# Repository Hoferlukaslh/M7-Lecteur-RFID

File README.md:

# M7-Lecteur-RFID
Ce dépôt contient l'ensemble des éléments du projet « Prototype de lecteur RFID » développé dans le cadre du module M7.    
L'objectif principal est de concevoir un système embarqué compact et bon marché, destiné à être dupliqué au sein des cellules de production des locaux de la NewTec.    
   
Ce système agit comme une interface physique et logique entre des tags RFID et un automate (PLC).   

[- Lien vers le dépot --](https://github.com/Hoferlukaslh/M7-Lecteur-RFID)

## Détails du projet 

### Architecture Globale et Communication
Le lecteur utilise une architecture de communication hybride pour s'adapter aux différents besoins de la ligne de production :

- Communication Automate (PLC) : Le système est universel et s'intègre avec tout type de contrôleur (Wago, Beckhoff, Raspberry Pi, etc.). Cette communication, servant à transmettre les ordres et les données lues, peut être activée ou désactivée selon les besoins de la cellule.

- Communication API (Wi-Fi) : De manière indépendante, le système interagit avec un serveur Node-RED via des requêtes API HTTP pour mettre à jour l'emplacement des palettes en temps réel dans une base de données. 

```mermaid
flowchart TD
    %% Définition des nœuds
    NR[Node-RED]
    DB[(BDD)]
    M7[Projet M7]
    PLC[Automate]

    %% Définition des liens et des étiquettes
    NR --> DB
    NR <-.->|"Requête API HTTP<br>(WiFi)<br>MàJ emplacement <br>palettes"| M7
    PLC -->|"Communication<br>pour ordres<br>(désactivable)"| M7
```

### Spécifications Matérielles
Le dispositif est conçu pour fonctionner de manière autonome dans un environnement industriel.

- Microcontrôleur : Choix libre.
- Module RFID : SBC-RFID-RC522.
- Connectivité : Wi-Fi avec antenne (choix libre).
- Alimentation : 24V DC (standard industriel).
- Cibles RFID : Petits disques de 15 mm x 3 mm disposant d'une capacité de stockage maximale de 106 octets.
- Intégration mécanique : Boîtier de protection imprimé en 3D. Il assure la sécurité du PCB et de l'antenne, tout en proposant un design universel pour une fixation rapide sur n'importe quelle structure machine sans gêner le flux des palettes.

### Spécifications Logicielles
Le firmware embarqué gère à la fois l'antenne RFID et la communication avec l'automate.  

#### Librairie RFID
Une bibliothèque logicielle est intégrée pour gérer la mémoire restreinte des tags avec les fonctions suivantes :

| Fonction | Description | 
| --- | --- |
| READ | Lecture des données présentes. |
| WRITE | Écriture avec écrasement du contenu existant. |
| APPEND | Ajout de nouvelles données à la suite (via gestion de pointeurs/marqueurs). |
| DELETE ALL | Effacement complet ou formatage du tag. |

#### Logique de Contrôle

| Fonction | Description | 
| --- | --- |
| Démarrage/Arrêt | Piloté sur commande du PLC. |
| Badge lu avec succès | Retour du contenu formaté au PLC et envoi de la mise à jour de position au serveur Node-RED. |
| Badge illisible/Erreur | Retour d'un code d'erreur spécifique au PLC. |
| Badge défectueux | Retour d'un code d'erreur critique (HS) au PLC. |
| Aucun badge | État d'attente, aucune action. |

### Ressources utilisées
#### Logiciels
| Logo | Application | Version | Utilité | Licence |
| :---: | :--- | :--- | :--- | --- |
|  | [**OnlyOffice**](https://www.onlyoffice.com) | 9.3.1 | Suite bureautique utilisée pour la rédaction et l’édition des documents du projet (DOCX, XLSX). | AGPL-3.0 |
|  | [**Draw.io**](https://github.com/jgraph/drawio) | 29.3.6 | Outil de conception de diagrammes. Utilisé pour la conception UML. | Apache 2.0 |
|  | [**VSCodium**](https://vscodium.com/) | v1.116.02821 | Editeur de texte avec extension (IDE) | MIT |
|  | [**Arduino IDE**](https://www.arduino.cc/en/software/) | 2.3.8 | IDE pour framework arduino (C++) | AGPL-3.0 |

### Modèle de Données et Optimisation
La contrainte matérielle majeure est la limite de 106 octets par tag. Une optimisation des données est indispensable.

#### Données des Palettes
- Identifiant de la palette.  
- Contenu de la palette : Jusqu'à 6 articles stockés sous le format `TTT-XXXXXX-VV-R` (Type de l'article, Code unique, Version, Révision).

#### Données des Badges Client :
- Identifiant de la palette.  
- Pseudonyme du client (10 caractères).  
- Données de production pour 4 cellules : Date, heure, et identifiant de la cellule ayant effectué l'opération.

## Livrables Attendus
L'arborescence de ce projet est divisée selon les livrables suivants :  

| Livrables | Description | 
| --- | --- |
| [Hardware](./Hardware/) | Dossier électronique contenant les schémas de principe, le routage PCB (fichiers Gerber) et la nomenclature (BOM). |
| [Mechanical](./Firmware/) | Fichiers 3D (STL/STEP) pour l'impression du boîtier de protection. |
| [Firmware](./Firmware/) | Code source documenté du microcontrôleur, incluant la pile de communication et la librairie RFID. |
| [Documents](./Documents/) | CdC et Journal, Documentation technique du projet (Table de communication décrivant le protocole PLC, les endpoints de l'API HTTP, et la cartographie d'optimisation mémoire) |
| [Images](./Images/) | Dossier contenant des images utilisés dans le projet. |

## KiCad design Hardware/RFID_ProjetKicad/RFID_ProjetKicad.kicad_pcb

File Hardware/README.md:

Dossier électronique contenant les schémas de principe, le routage PCB (fichiers Gerber) et la nomenclature (BOM).

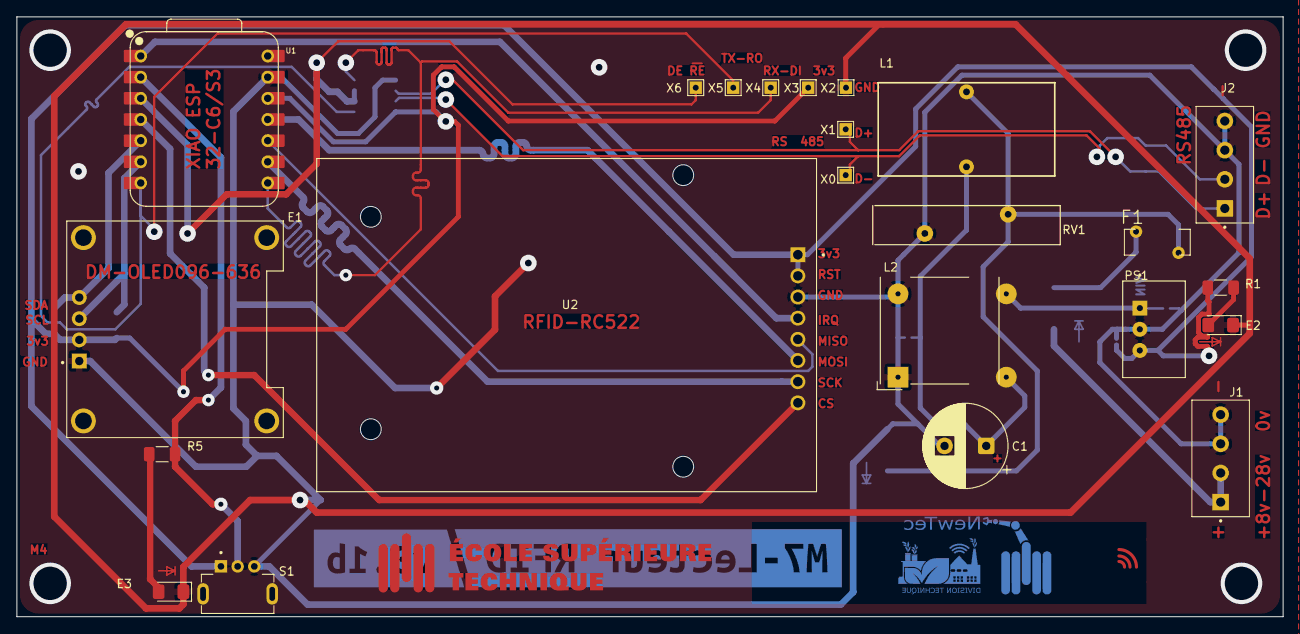
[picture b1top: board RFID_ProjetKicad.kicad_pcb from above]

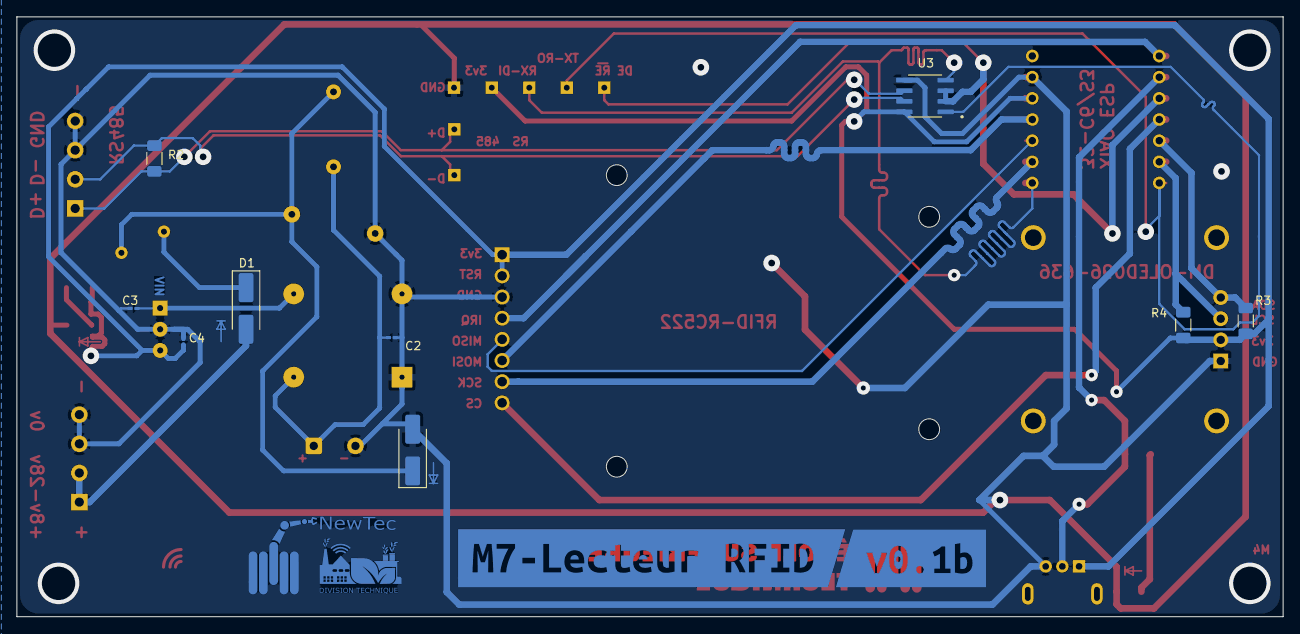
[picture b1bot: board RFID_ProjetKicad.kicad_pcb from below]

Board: 2 copper layers, 152.0 x 72.0 mm, 34 parts (11 on the bottom side), 22 nets.

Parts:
C1: 470µF; CP_Radial_D10.0mm_P5.00mm
C2: 4.7μF; C_0201_0603Metric_Pad0.64x0.40mm_HandSolder
C3: 10µF; C_0201_0603Metric_Pad0.64x0.40mm_HandSolder
C4: 22µF; C_0201_0603Metric_Pad0.64x0.40mm_HandSolder
D1: BX36_R1; D_SMA_Handsoldering
D2: SMAJ28A; D_SMA_Handsoldering
E1: DM-OLED096-636; MODULE_DM-OLED096-636
E2, E3: LED; LED_1206_3216Metric_Pad1.42x1.75mm_HandSolder
F1: PTC 1A; PTC
J1, J2: TB0011-350-04GR; SAMESKY_TB0011-350-04GR
L1: 300 µH; WE-FI_7447060
L2: 5 mH; SS11VL-11050
PS1: TSR_1-2433E; CONV_TSR_1-2433E
R1, R5: 68 R; R_1206_3216Metric_Pad1.30x1.75mm_HandSolder
R2: 120 R; R_1206_3216Metric_Pad1.30x1.75mm_HandSolder
R3, R4: 4k7; R_1206_3216Metric_Pad1.30x1.75mm_HandSolder
RV1: 20D470K; RV_Disc_D12mm_W4.7mm_P7.5mm
S1: SLW-874744; SW_SLW-874744-6A-RA-N-D
U1: XIAO-ESP32-C6-DIP
U2: RFID-RC522; MODULE_CEG006900
U3: MAX3485CSA_T; SOIC127P600X175-8N
X0, X1, X2, X3, X4, X5, X6: TestPoint_THTPad_1.5x1.5mm_Drill0.7mm
kibuzzard-6A1B3F22: G***; kibuzzard-6A1B3F22
kibuzzard-69FBB4E7: G***; kibuzzard-69FBB4E7

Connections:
+3V3: C4.1, E1.2 (VCC_IN), PS1.3 (+VOUT), R1.1, R3.1, R4.1, S1.1, U1.12 (3V3), U2.1 (VCC), U2.2 (RST), U3.8 (VCC), X3.1
+7V à 27.6V: D2.1 (A1), F1.2, L1.1, RV1.1
+8V à 28V: D1.2 (A), J1.1, J1.2
/D+: J2.1, R2.2, U3.6 (A), X1.1
/D-: J2.2, R2.1, U3.7 (B), X0.1
/SW_COM: R5.2, S1.2, U1.2 (GPIO1_A1_D1)
GND: C1.2, C2.2, C3.2, C4.2, D2.2 (A2), E1.1 (GND), E2.1 (K), E3.1 (K), J1.3, J1.4, J2.3, J2.4, L2.1, L2.4, PS1.2 (GND), RV1.2, S1.3, U1.13 (GND), U2.3 (GND), U3.5 (GND), X2.1
unnamed: C1.1, C2.1, L1.2, L2.2
unnamed: D1.1 (K), F1.1
unnamed: E1.3 (SCL), R4.2, U1.6 (GPIO23_D5_SCL)
unnamed: E1.4 (SDA), R3.2, U1.5 (GPIO22_D4_SDA)
unnamed: E2.2 (A), R1.2
unnamed: E3.2 (A), R5.1
unnamed: C3.1, L2.3, PS1.1 (+VIN)
unnamed: U1.1 (GPIO0_A0_D0), U2.4 (IRQ)
unnamed: U1.3 (GPIO2_A2_D2), U3.2 (~RE), U3.3 (DE), X6.1
unnamed: U1.7 (GPIO16_D6_TX), U3.1 (RO), X5.1
unnamed: U1.8 (GPIO17_D7_RX), U3.4 (DI), X4.1
unnamed: U1.11 (GPIO18_D10_MOSI), U2.6 (MOSI)
unnamed: U1.9 (GPIO19_D8_SCK), U2.7 (SCK)
unnamed: U1.10 (GPIO20_D9_MISO), U2.5 (MISO/SCL/TX)
unnamed: U1.4 (GPIO21_D3), U2.8 (SS/SDA/RX)

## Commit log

2026-04-30 Ajout des différents documents
2026-04-30 Ajout des repertoires
2026-04-30 Ajout dossier
2026-04-30 Ajout gitIgnore
2026-04-30 Déplacement gitIgnore
2026-04-30 renomer Gitignore
2026-04-30 ajout concept détaillé
2026-04-30 Correction git
2026-05-01 Ajout choix composants
2026-05-01 Ajout des différentes recherches
    Ajout composant + list mat, ajout datasheet, ajout images
2026-05-04 Ajout de documents
    Schematic KiCad + modification rapport
2026-05-04 Correction GitHub
    Readme, gitIgnore, suppression fichiers inutiles
2026-05-04 Création de la librairie du projet
    Fusion des bibliotheques + suppression fichier inutiles
2026-05-04 Ajout du schéma prototype d'ensemble
2026-05-05 Refactor de l'alimentation
2026-05-05 modification liste matériel avec lien vers datasheet
2026-05-05 Suppression de fichiers inutiles
2026-05-05 Ajout de footprint + STEP files
2026-05-05 Correction schéma et footprint
    Test PCB 3D : OKEY!
2026-05-05 Mise a jour de la documentation technique
2026-05-05 Remise du gitIgnore
    Fausse manip
2026-05-06 Création du PCB
    placement, routage et controle
2026-05-06 Correction PCB + Logos
2026-05-06 Ajout de points de test sur PCB
2026-05-06 Ajout de la documentation sur l'implémentation PCB + Modification PCB et logos
2026-05-06 Ajout de la fiche signalétique du projet
2026-05-07 Correction de la violation de la RDC
    Modification PCB
2026-05-07 Ajout des choix pour le software
2026-05-17 Ajout commande mat
2026-05-30 Agrandissement des taille des pads
